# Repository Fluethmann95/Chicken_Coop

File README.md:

# Hühnerklappensteuerung

- Vollautomatische Steuerung für Stalltüren
- Möglichkeit der Ansteuerung über verschiedene Wege:
	- Am Gerät einstellbarer Zeit für Öffnen und Schließen
	- Helligkeit über externen Sensor
	- Handbetrieb per Drucktaster
- Einstellbare Fahrtzeit in 1/10 Sekunden
- Einstellbare Uhrzeit
- Anschluss für User-Button und Poti
- Diagnose und Konfiguration über LCD und RGB-LED
- 2 Anschlussmöglichkeiten für PNP/NPN Endstops
- Automatische Zeitsynchronisation bei Upload mit PC Zeit
- Update des Codes über SD Karte

##Technische Details
- Arduino MKRZERO µC-Board
- Zeitmessung über DS3231 RTC
- Solar Laderegler mit automatisch geregelter Ladespannung
- PWM Motorausgang mit Strommessung und H-Brücke
- Batteriemanagement

##Aktuelle Konfiguration
- Fahrtdauer 250 s/10
- Öffnen 5:20 Uhr
- Schließen 22:10 Uhr

##Benötigtes Material
- Steuerungsplatine inkl passendem Gehäuse (RND-455 00265)
- Elektromotor 12V mit passendem Getriebe und Seilrolle
- Solarpanel 12V 20Wmax.
- Bleigelbatterie ~10Ah

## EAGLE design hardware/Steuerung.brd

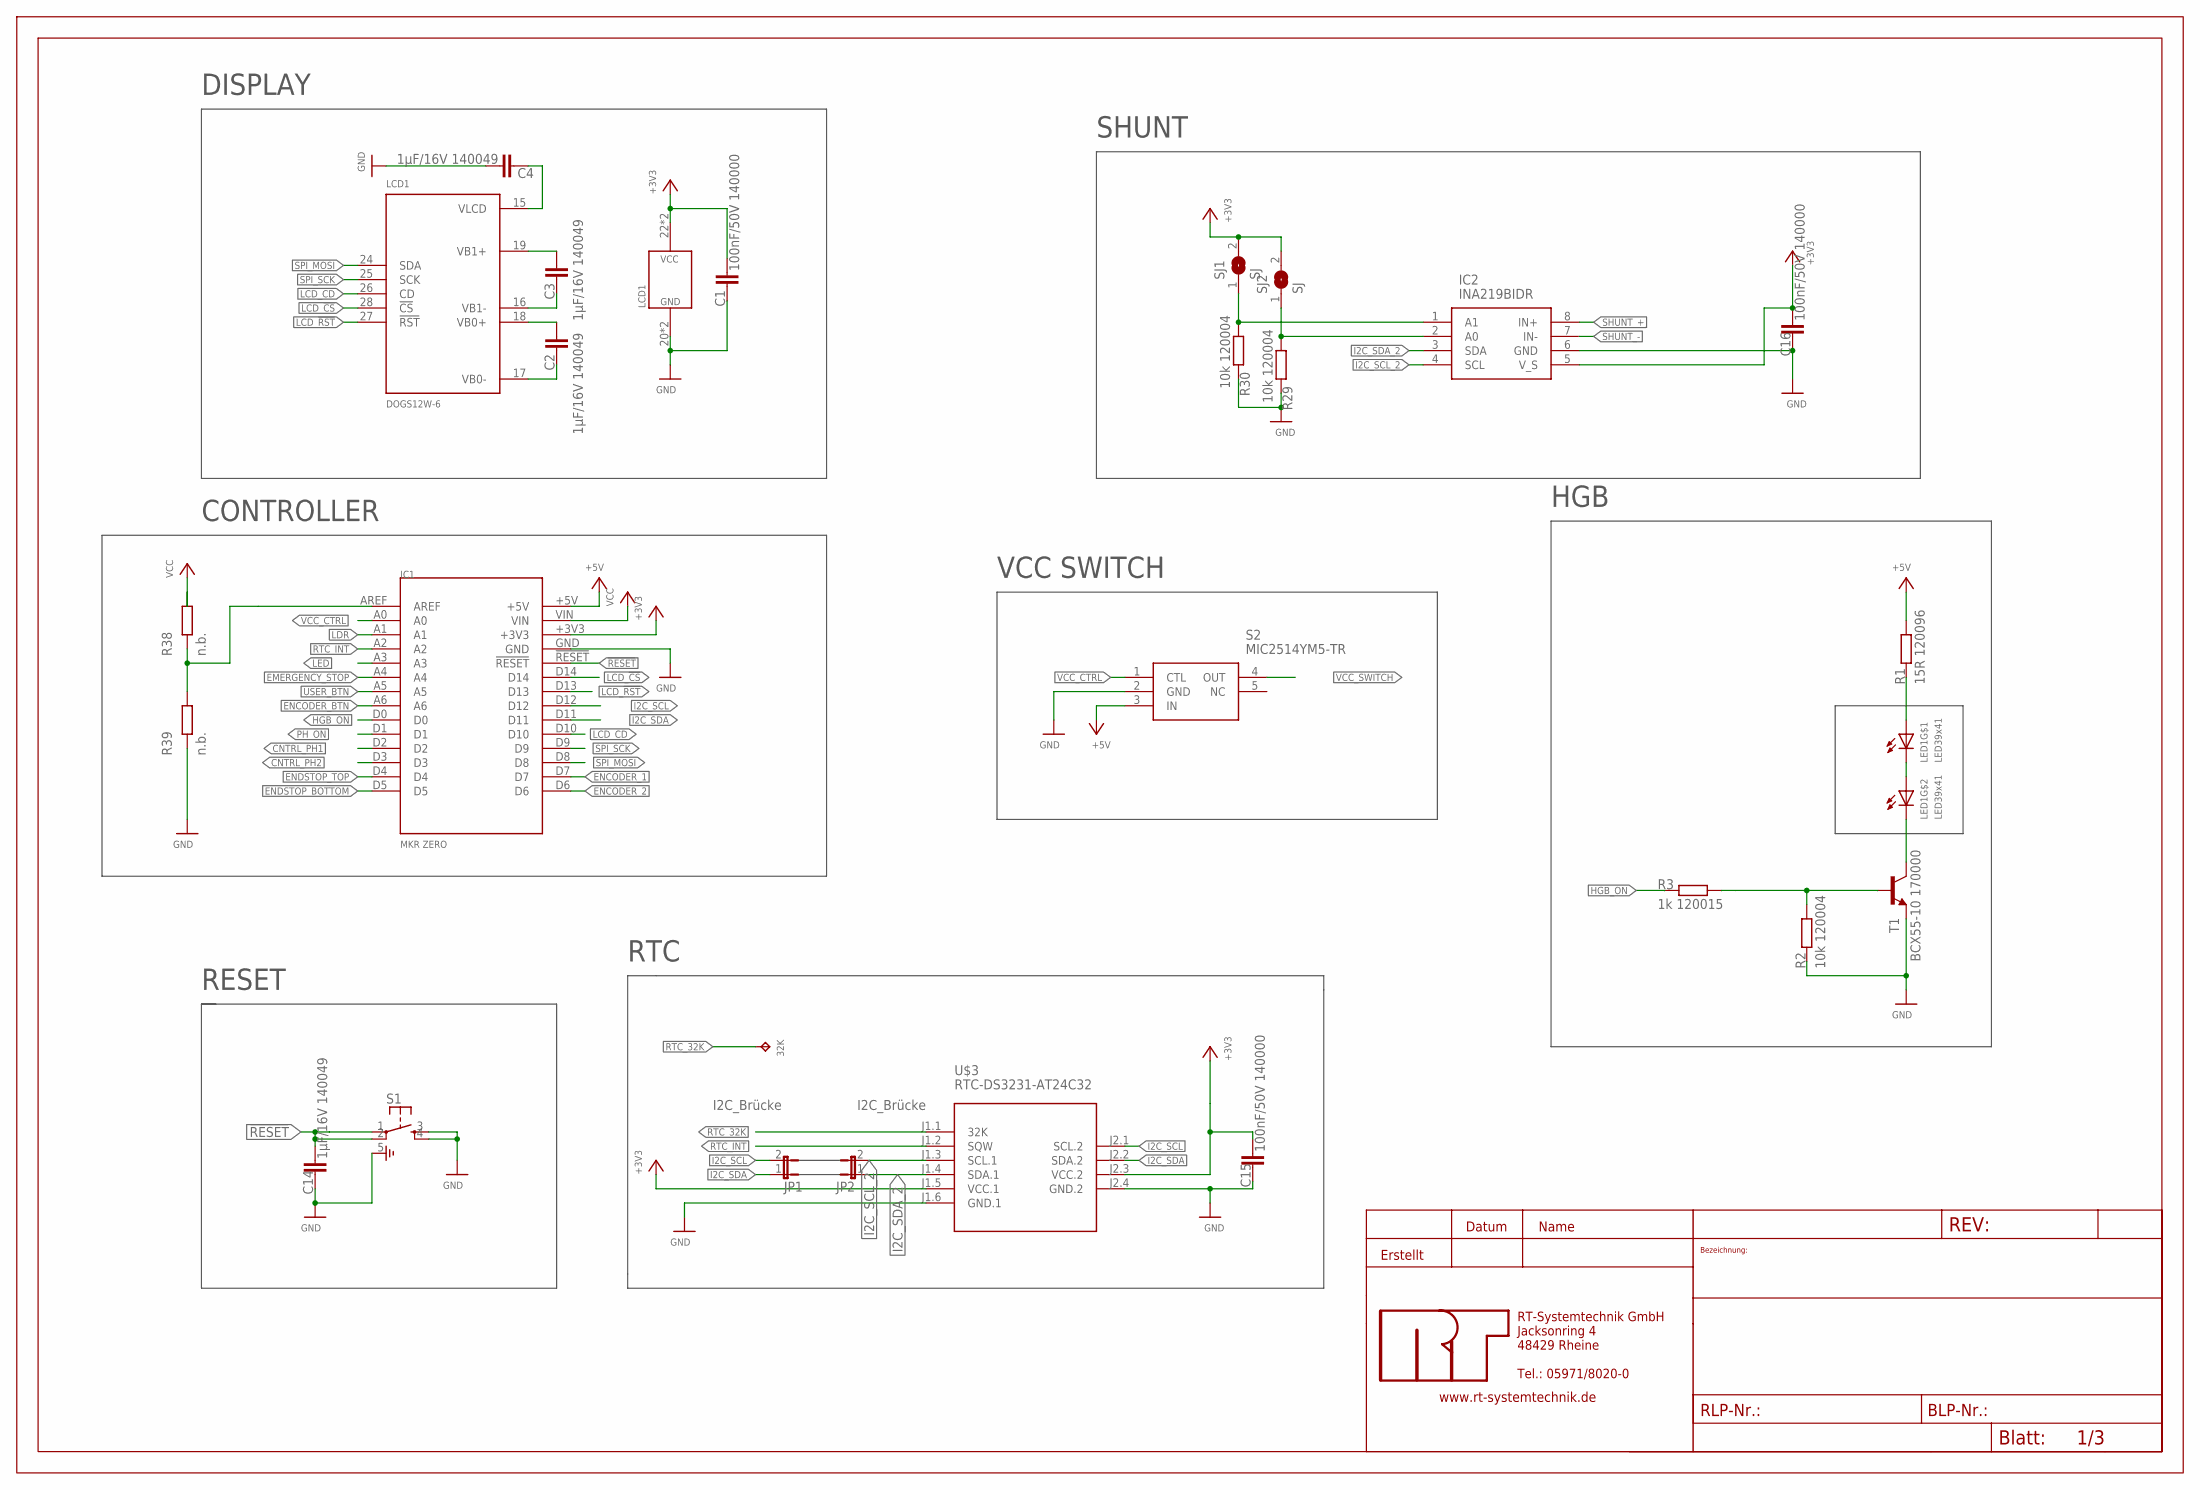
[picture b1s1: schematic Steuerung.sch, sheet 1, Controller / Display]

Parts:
32K: PAD_SMD_2,5X1; SMD_2,5X1
C1, C15, C16: 100nF/50V 140000; C0805
C2, C3, C4, C14: 1µF/16V 140049; C0805
FRAME1: A3L-LOC; DOKUDATA
IC1: MKR ZERO; MKR_ZERO
IC2: INA219BIDR; SOIC127P600X175-8N
JP1, JP2: I2C_Brücke; JP1
LCD1: DOGS12W-6; DOGS_LCD_102X64
LED1: LED39x41; LED39X41
R1: 15R 120096; R0805
R2, R29, R30: 10k 120004; R0805
R3: 1k 120015; R0805
R38, R39: n.b.; R0805
S1: B3SN-3X12; B3SN-3X12_SMD
S2: MIC2514YM5-TR; SOT95P280X130-5N
SJ1, SJ2: SJ
T1: BCX55-10 170000; SOT89-BCE
U$3: RTC-DS3231-AT24C32

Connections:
!RESET: C14.1, IC1.!RESET, S1.1, S1.2 (P1)
+3V3: C1.1, C15.1, C16.1, IC1.+3V3, IC2.5 (V_S), LCD1.22 (VCC), LCD1.23 (VCC), SJ1.2, SJ2.2, U$3.J1.5 (VCC.1), U$3.J2.3 (VCC.2); also elsewhere on the board
+5V: IC1.+5V, R1.1, S2.3 (IN); also elsewhere on the board
CNTRL_PH1: IC1.D2; also elsewhere on the board
CNTRL_PH2: IC1.D3; also elsewhere on the board
EMERGENCY_STOP: IC1.A4; also elsewhere on the board
ENCODER_1: IC1.D7; also elsewhere on the board
ENCODER_2: IC1.D6; also elsewhere on the board
ENCODER_BTN: IC1.A6; also elsewhere on the board
ENDSTOP_BOTTOM: IC1.D5; also elsewhere on the board
ENDSTOP_TOP: IC1.D4; also elsewhere on the board
GND: C1.2, C4.1, C14.2, C15.2, C16.2, IC1.GND, IC2.6 (GND), LCD1.20 (GND), LCD1.21 (GND), R2.2, R29.1, R30.1, R39.2, S1.3 (S), S1.4 (S1), S1.5, S2.2 (GND), T1.E, U$3.J1.6 (GND.1), U$3.J2.4 (GND.2); also elsewhere on the board
HGB_ON: IC1.D0, R3.2
I2C_SCL: IC1.D12, JP1.2, U$3.J2.1 (SCL.2); also elsewhere on the board
I2C_SCL_2: IC2.4 (SCL), JP2.2, U$3.J1.3 (SCL.1)
I2C_SDA: IC1.D11, JP1.1, U$3.J2.2 (SDA.2); also elsewhere on the board
I2C_SDA_2: IC2.3 (SDA), JP2.1, U$3.J1.4 (SDA.1)
LCD_!CS: IC1.D14, LCD1.28 (!CS)
LCD_!RST: IC1.D13, LCD1.27 (!RST)
LCD_CD: IC1.D10, LCD1.26 (CD)
LDR: IC1.A1; also elsewhere on the board
LED: IC1.A3; also elsewhere on the board
unnamed: C3.1, LCD1.19 (VB1+)
unnamed: C3.2, LCD1.16 (VB1-)
unnamed: C2.1, LCD1.18 (VB0+)
unnamed: C2.2, LCD1.17 (VB0-)
unnamed: C4.2, LCD1.15 (VLCD)
unnamed: LED1.2 (C), LED1.14 (A)
unnamed: LED1.1 (A), R1.2
unnamed: LED1.13 (C), T1.C
unnamed: R2.1, R3.1, T1.B
unnamed: IC2.1 (A1), R30.2, SJ1.1
unnamed: IC2.2 (A0), R29.2, SJ2.1
unnamed: IC1.AREF, R38.2, R39.1
PH_ON: IC1.D1; also elsewhere on the board
RTC_32K: 32K.PIN1, U$3.J1.1 (32K)
RTC_INT: IC1.A2, U$3.J1.2 (SQW)
SHUNT_+: IC2.8 (IN+); also elsewhere on the board
SHUNT_-: IC2.7 (IN-); also elsewhere on the board
SPI_MOSI: IC1.D8, LCD1.24 (SDA)
SPI_SCK: IC1.D9, LCD1.25 (SCK)
USER_BTN: IC1.A5; also elsewhere on the board
VCC: IC1.VIN, R38.1; also elsewhere on the board
VCC_CTRL: IC1.A0, S2.1 (CTL)
VCC_SWITCH: S2.4 (OUT); also elsewhere on the board

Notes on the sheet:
HGB
SHUNT
DISPLAY
CONTROLLER
RESET
RTC
VCC SWITCH

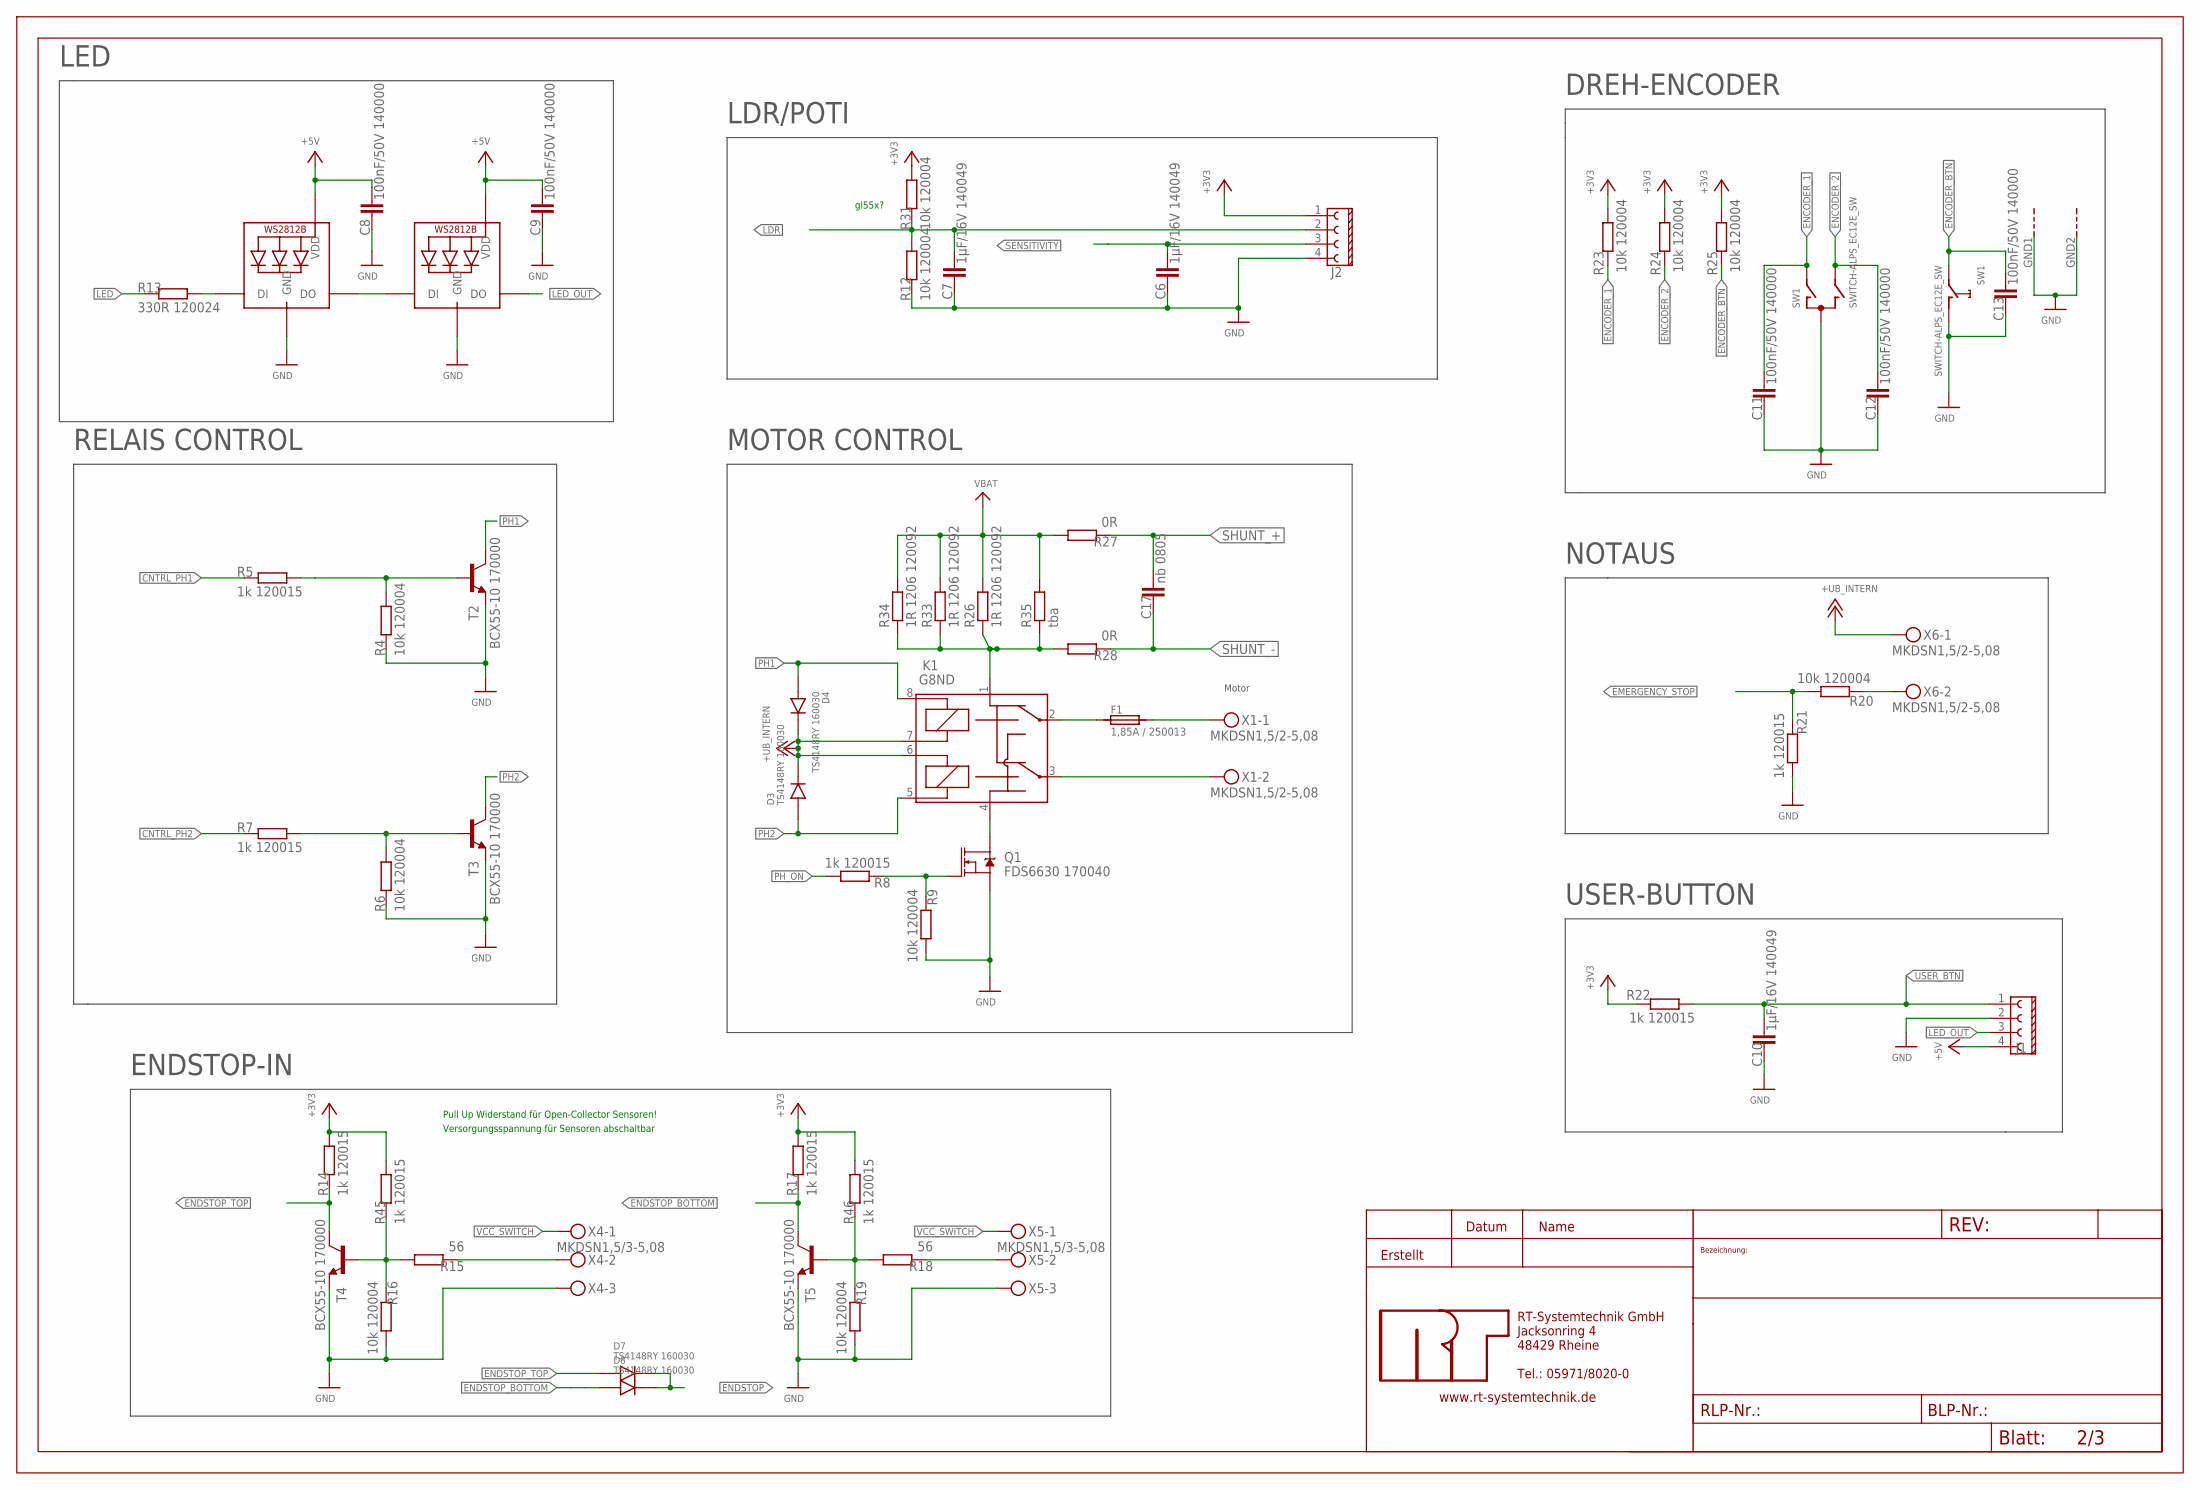
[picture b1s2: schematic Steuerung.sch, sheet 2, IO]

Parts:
C6, C7, C10: 1µF/16V 140049; C0805
C8, C9, C11, C12, C13: 100nF/50V 140000; C0805
C17: nb 0805; C0805
D3, D4, D7, D8: TS4148RY 160030; R1206
F1: 1,85A / 250013; SMD2920
FRAME2: A3L-LOC; DOKUDATA
J1, J2: CONNECTORS_JST-4; CONNECTORS_EXH_PRN_H_INV
K1: G8ND; RELAYS_OMRON_G8ND2
LED2, LED3: WS2812B5050; WS2812B
Q1: FDS6630 170040; SO08
R4, R6, R9, R12, R16, R19, R20, R23, R24, R25, R31: 10k 120004; R0805
R5, R7, R8, R14, R17, R21, R22, R45, R46: 1k 120015; R0805
R13: 330R 120024; R0805
R15, R18: 56; R0805
R26, R33, R34: 1R 1206 120092; R1206W
R27, R28: 0R; R0805
R35: tba; 0207/7
SW1: SWITCH-ALPS_EC12E_SW; SWITCH-ALPS_ALPS_EC12E_SW
T2, T3, T4, T5: BCX55-10 170000; SOT89-BCE
X1, X6: MKDSN1,5/2-5,08
X4, X5: MKDSN1,5/3-5,08

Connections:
+3V3: J2.1, R14.1, R17.1, R22.2, R23.1, R24.1, R25.1, R31.1, R45.1, R46.1; also elsewhere on the board
+5V: C8.1, C9.1, J1.4, LED2.1-VDD (VDD), LED3.1-VDD (VDD); also elsewhere on the board
+UB_INTERN: D3.2 (C), D4.2 (C), K1.6 (2SA), K1.7 (1SB), X6.1; also elsewhere on the board
CNTRL_PH1: R5.2; also elsewhere on the board
CNTRL_PH2: R7.2; also elsewhere on the board
EMERGENCY_STOP: R20.1, R21.2; also elsewhere on the board
ENCODER_1: C11.1, R23.2, SW1.A; also elsewhere on the board
ENCODER_2: C12.1, R24.2, SW1.B; also elsewhere on the board
ENCODER_BTN: C13.1, R25.2, SW1.E (2); also elsewhere on the board
ENDSTOP: D7.2 (C), D8.2 (C); also elsewhere on the board
ENDSTOP_BOTTOM: D8.1 (A), R17.2, T5.C; also elsewhere on the board
ENDSTOP_TOP: D7.1 (A), R14.2, T4.C; also elsewhere on the board
GND: C6.2, C7.2, C8.2, C9.2, C10.2, C11.2, C12.2, C13.2, J1.2, J2.4, LED2.3-GND (GND), LED3.3-GND (GND), Q1.1 (S), Q1.2 (S), Q1.3 (S), R4.2, R6.2, R9.1, R12.2, R16.1, R19.1, R21.1, SW1.C, SW1.D (1), SW1.GND1 (G), SW1.GND2 (G), T2.E, T3.E, T4.E, T5.E, X4.3, X5.3; also elsewhere on the board
LDR: C7.1, J2.2, R12.1, R31.2; also elsewhere on the board
LED: R13.2; also elsewhere on the board
LED_OUT: J1.3, LED3.2-DOUT (DO)
unnamed: K1.4 (O2), Q1.5 (D), Q1.6 (D), Q1.7 (D), Q1.8 (D)
unnamed: Q1.4 (G), R8.2, R9.2
unnamed: R4.1, R5.1, T2.B
unnamed: R6.1, R7.1, T3.B
unnamed: K1.3 (P2), X1.2
unnamed: F1.1, K1.2 (P1)
unnamed: F1.2, X1.1
unnamed: LED2.4-DIN (DI), R13.1
unnamed: LED2.2-DOUT (DO), LED3.4-DIN (DI)
unnamed: R15.1, R16.2, R45.2, T4.B
unnamed: R15.2, X4.2
unnamed: R18.1, R19.2, R46.2, T5.B
unnamed: R18.2, X5.2
unnamed: K1.1 (O1), R26.1, R28.1, R33.1, R34.1, R35.1
unnamed: R20.2, X6.2
PH1: D4.1 (A), K1.8 (1SA), T2.C
PH2: D3.1 (A), K1.5 (2SB), T3.C
PH_ON: R8.1; also elsewhere on the board
SENSITIVITY: C6.1, J2.3; also elsewhere on the board
SHUNT_+: C17.1, R27.2; also elsewhere on the board
SHUNT_-: C17.2, R28.2; also elsewhere on the board
USER_BTN: C10.1, J1.1, R22.1; also elsewhere on the board
VBAT: R26.2, R27.1, R33.2, R34.2, R35.2; also elsewhere on the board
VCC_SWITCH: X4.1, X5.1; also elsewhere on the board

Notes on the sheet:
Motor
gl55x?
LED
LDR/POTI
DREH-ENCODER
NOTAUS
MOTOR CONTROL
RELAIS CONTROL
ENDSTOP-IN
USER-BUTTON
Pull Up Widerstand für Open-Collector Sensoren!
Versorgungsspannung für Sensoren abschaltbar

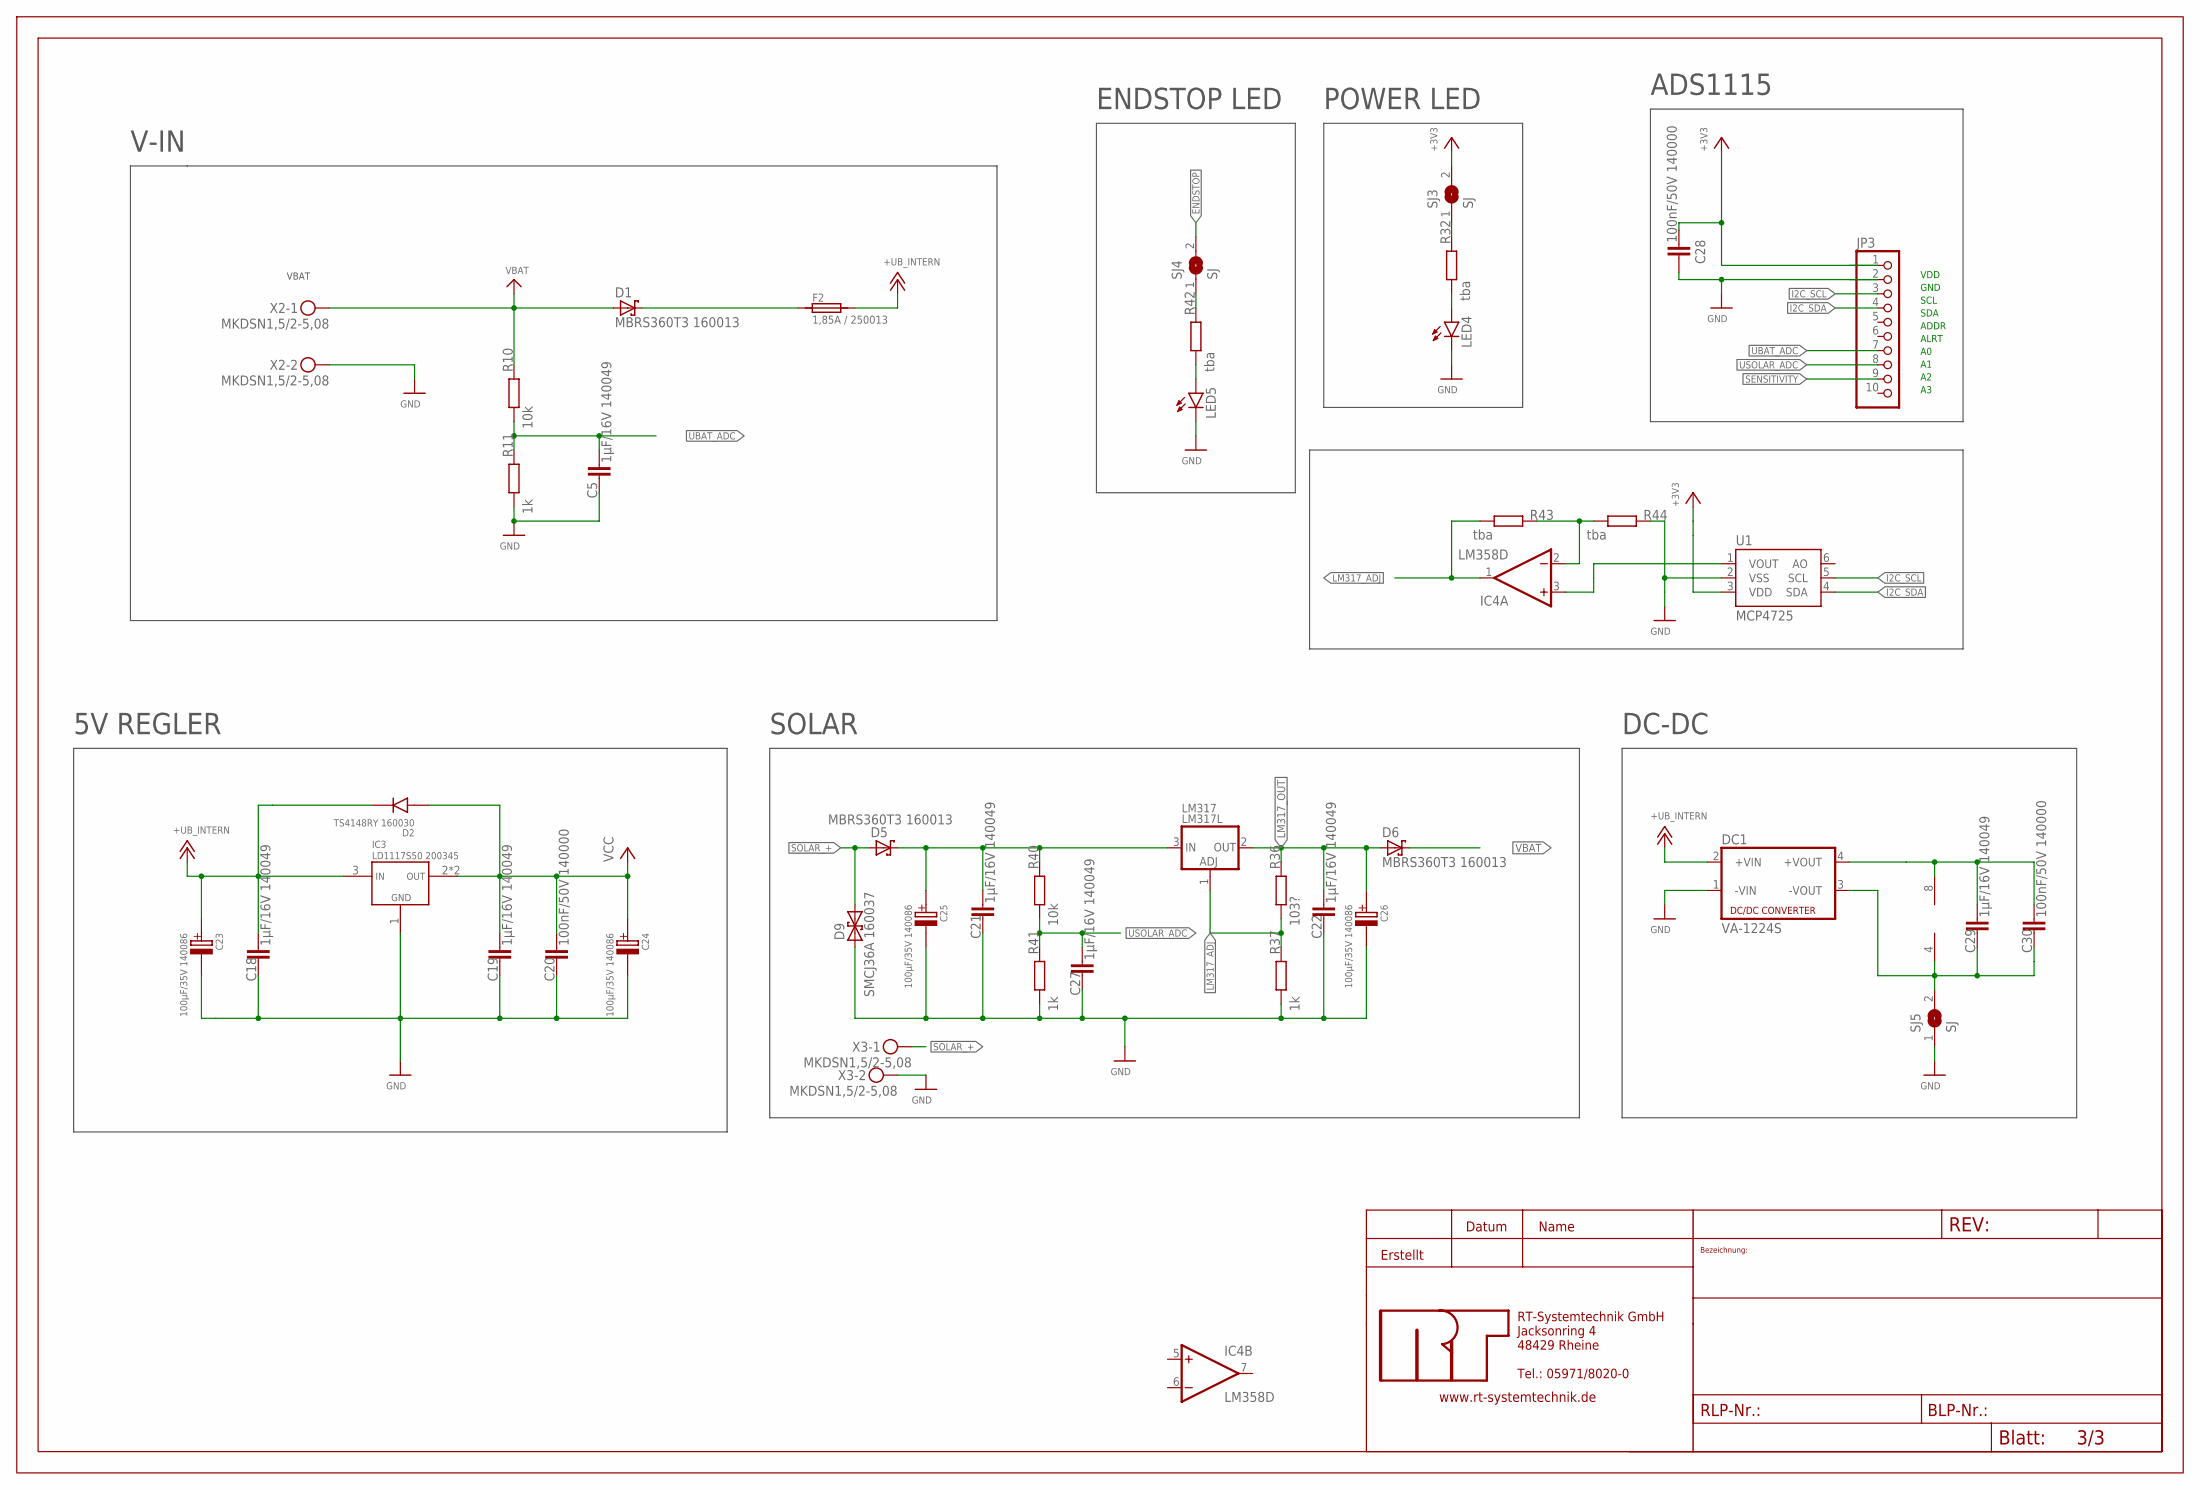
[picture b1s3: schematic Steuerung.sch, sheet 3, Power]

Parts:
C5, C18, C19, C21, C22, C27, C29: 1µF/16V 140049; C0805
C20, C28, C30: 100nF/50V 140000; C0805
C23, C24, C25, C26: 100µF/35V 140086; RCL_CE_D
D1, D5, D6: MBRS360T3 160013; ROLF_SMC
D2: TS4148RY 160030; R1206
D9: SMCJ36A 160037; SMC
DC1: VA-1224S; 4SIL
F2: 1,85A / 250013; SMD2920
FRAME3: A3L-LOC; DOKUDATA
IC3: LD1117S50 200345; SPANNUNGSREGLER_SOT-223
IC4: LM358D; SO08
JP3: PINHD-1X10; 1X10
LED4, LED5: LEDCHIP-LED0805; CHIP-LED0805
LM317: LM317L; TO220L
R10, R40: 10k; R0805
R11, R37, R41: 1k; R0805
R32, R42, R43, R44: tba; R0805
R36: 103?; R0805
SJ3, SJ4, SJ5: SJ
U1: MCP4725; SOT23-6
X2, X3: MKDSN1,5/2-5,08

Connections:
+3V3: C28.1, JP3.1, SJ3.2, U1.3 (VDD); also elsewhere on the board
+UB_INTERN: C18.1, C23.+, D2.2 (C), DC1.2 (+VIN), F2.2, IC3.3 (IN); also elsewhere on the board
ENDSTOP: SJ4.2; also elsewhere on the board
GND: C5.2, C18.2, C19.2, C20.2, C21.2, C22.2, C23.-, C24.-, C25.-, C26.-, C27.2, C28.2, D9.A (1), DC1.1 (-VIN), IC3.1 (GND), JP3.2, LED4.C, LED5.C, R11.2, R37.2, R41.2, R44.1, U1.2 (VSS), X2.2, X3.2; also elsewhere on the board
I2C_SCL: JP3.3, U1.5 (SCL); also elsewhere on the board
I2C_SDA: JP3.4, U1.4 (SDA); also elsewhere on the board
LM317_ADJ: IC4.1 (OUT), LM317.1 (ADJ), R36.2, R37.1, R43.2
LM317_OUT: C22.1, C26.+, D6.A, LM317.2 (OUT), R36.1
unnamed: D1.K, F2.1
unnamed: LED4.A, R32.2
unnamed: C21.1, C25.+, D5.K, LM317.3 (IN), R40.1
unnamed: R32.1, SJ3.1
unnamed: IC4.3 (+IN), U1.1 (VOUT)
unnamed: LED5.A, R42.2
unnamed: R42.1, SJ4.1
unnamed: C29.1, C30.1, DC1.4 (+VOUT), IC4.8 (V+)
unnamed: IC4.2 (-IN), R43.1, R44.2
unnamed: C29.2, C30.2, DC1.3 (-VOUT), IC4.4 (V-), SJ5.2
SENSITIVITY: JP3.9; also elsewhere on the board
SOLAR_+: D5.A, D9.C (2), X3.1
UBAT_ADC: C5.1, JP3.7, R10.2, R11.1
USOLAR_ADC: C27.1, JP3.8, R40.2, R41.1
VBAT: D1.A, D6.K, R10.1, X2.1; also elsewhere on the board
VCC: C19.1, C20.1, C24.+, D2.1 (A), IC3.2 (OUT), IC3.4 (OUT); also elsewhere on the board

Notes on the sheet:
VBAT
5V REGLER
V-IN
SOLAR
POWER LED
VDD GND SCL SDA ADDR ALRT A0 A1 A2 A3
ENDSTOP LED
ADS1115
DC-DC

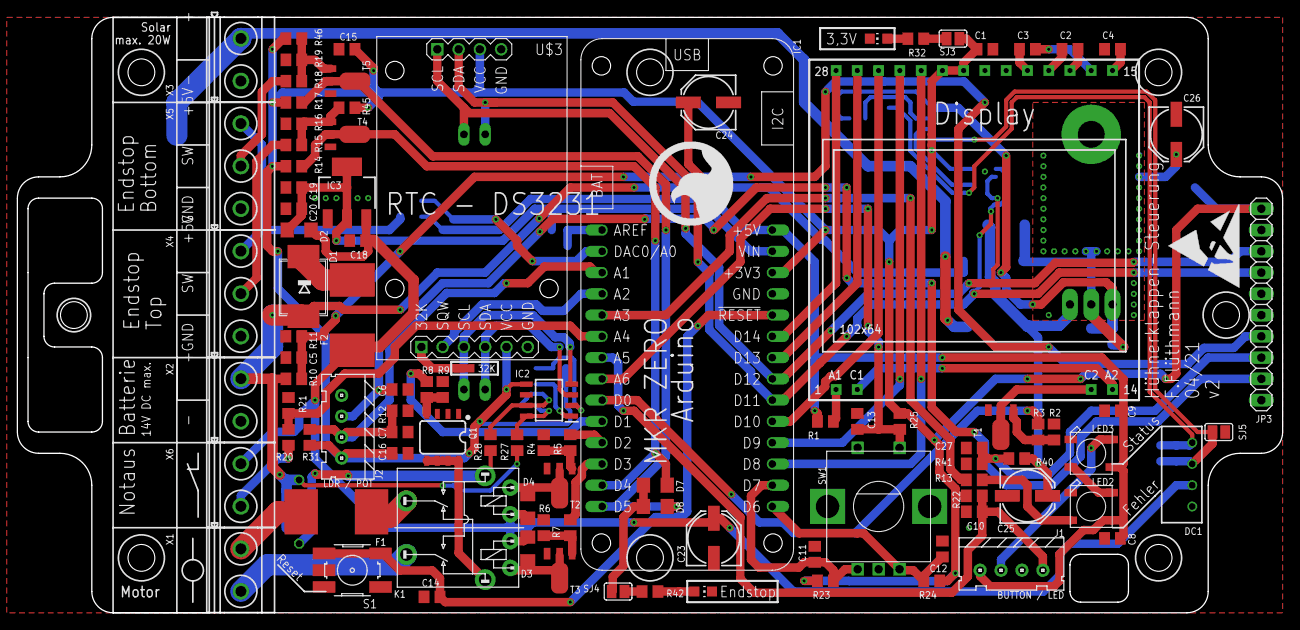
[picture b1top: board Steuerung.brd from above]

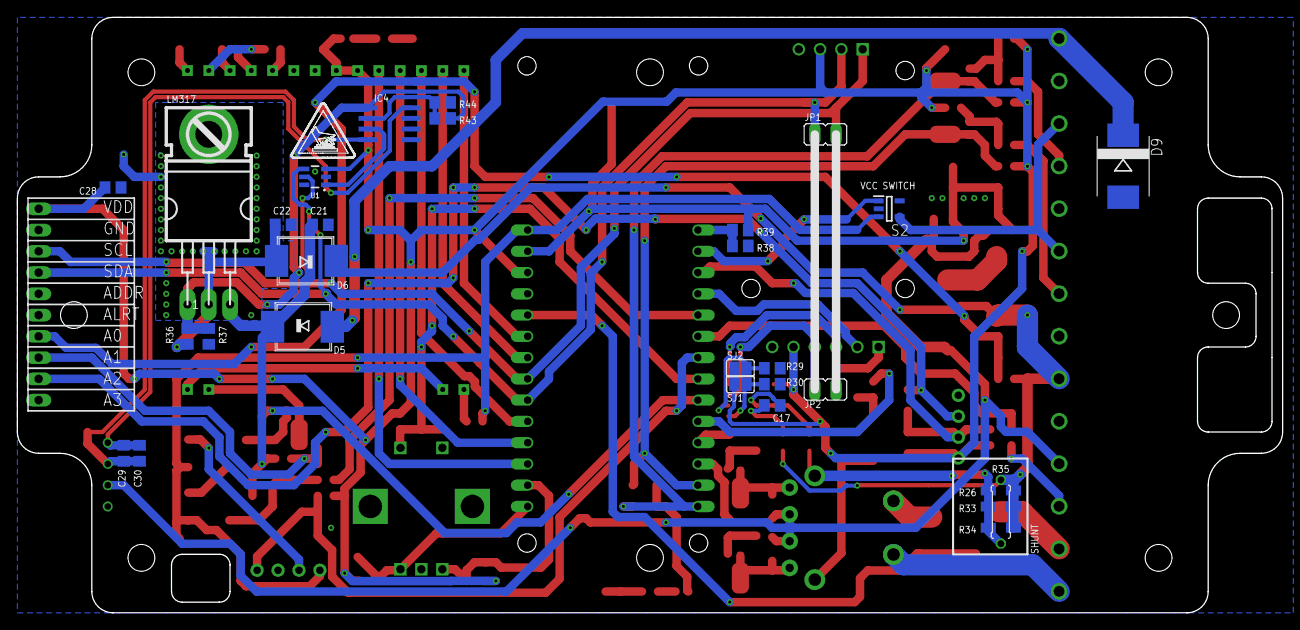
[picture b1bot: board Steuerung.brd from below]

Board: 2 copper layers, 151.1 x 71.1 mm, 133 parts (29 on the bottom side), 82 nets.

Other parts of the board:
U$4: ESD_10.00
U$5: CS-2016-LOGO-10MM

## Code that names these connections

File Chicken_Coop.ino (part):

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

//Defines
#define HGB_ON 0          //Ansteuerung Display Hintergrundbeleuchtung HIGH Aktiv -OUT PWM
#define PH_ON 1           //PWM Ansteuerung Motorphase HIGH Aktiv -OUT PWM
#define CNTRL_PH1 2       //Umschaltung Anschluss X1-1 HIGH Aktiv -OUT
#define CNTRL_PH2 3       //Umschaltung Anschluss X1-2 HIGH Aktiv -OUT
#define ENDSTOP_TOP 4     //Anschluss X4 HIGH Aktiv -IN
#define ENDSTOP_BOTTOM 5  //Anschluss X5 HIGH Aktiv -IN
#define ENCODER_2 6       //Drehencoder -IN LIB
#define ENCODER_1 7       //Drehencoder -IN LIB
#define SPI_MOSI 8        //SPI BUS MOSI LIB
#define SPI_SCK 9         //SPI BUS SCK LIB
#define LCD_CD 10         //Umschaltung Command<->Data Display -OUT LIB
#define I2C_SDA 11        //I2C BUS Data LIB
#define I2C_SCL 12        //I2C BUS Clock LIB
#define LCD_RST 13        //LCD Reset -OUT LIB
#define LCD_CS 14         //SPI BUS Chip Select LCD -OUT LIB
#define VCC_CTRL A0       //Schalten der Endstop-Versorgungsspannung HIGH Aktiv -OUT
#define LDR A1            //Erkennung Helligkeit über LDR -IN ANALOG
#define RTC_INT A2        //Programmierbarer Interrupt der RTC -IN
#define LED_PIN A3        //WS2812 Ausgang -OUT LIB
#define NOTAUS A4         //NOTAUS Eingang LOW Aktiv -IN
#define USER_BTN A5       //User Taster Eingang LOW Aktiv -IN
#define ENCODER_BTN A6    //Button des Drehencoders LOW Aktiv Interner Pullup -IN



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ADS1115_WE adc = ADS1115_WE(I2C_ADDRESS);
float UBAT = 0;         //Channel A0
float USOLAR = 0;       //Channel A1
float SENSITIVITY = 0;  //Channel A2
//Channel A3 des ADC ist frei

//DAC
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
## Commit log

2022-07-20 Releaseversion
    Installation am 19.7.22
2022-07-20 Update README.md
    Erstellt mit https://pandao.github.io/editor.md/en.html
2022-07-20 PCB Files hinzugefügt
2022-07-20 Handbetrieb Ablauf geändert
2022-07-21 Release 20.7.
    Überstrom & NOTAUS Abschaltung deaktiviert (Hat Probleme bereitet)
2023-03-06 Umbenannt
    Umbenannt um Arduino Namensregeln zu entsprechen
    Hex Files hinzugefügt
2023-03-06 SD Log hinzugefügt

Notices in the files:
parts and their libraries:
SparkFun-DiscreteSemi: Licensing: Creative Commons ShareAlike 4.0 International - https://creativecommons.org/licenses/by-sa/4.0
diy-modules: Released under the Creative Commons Attribution 4.0 International License: http://creativecommons.org/licenses/by/4.0
